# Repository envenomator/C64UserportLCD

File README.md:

# C64userport

C64 Userport LCD & LED breakout

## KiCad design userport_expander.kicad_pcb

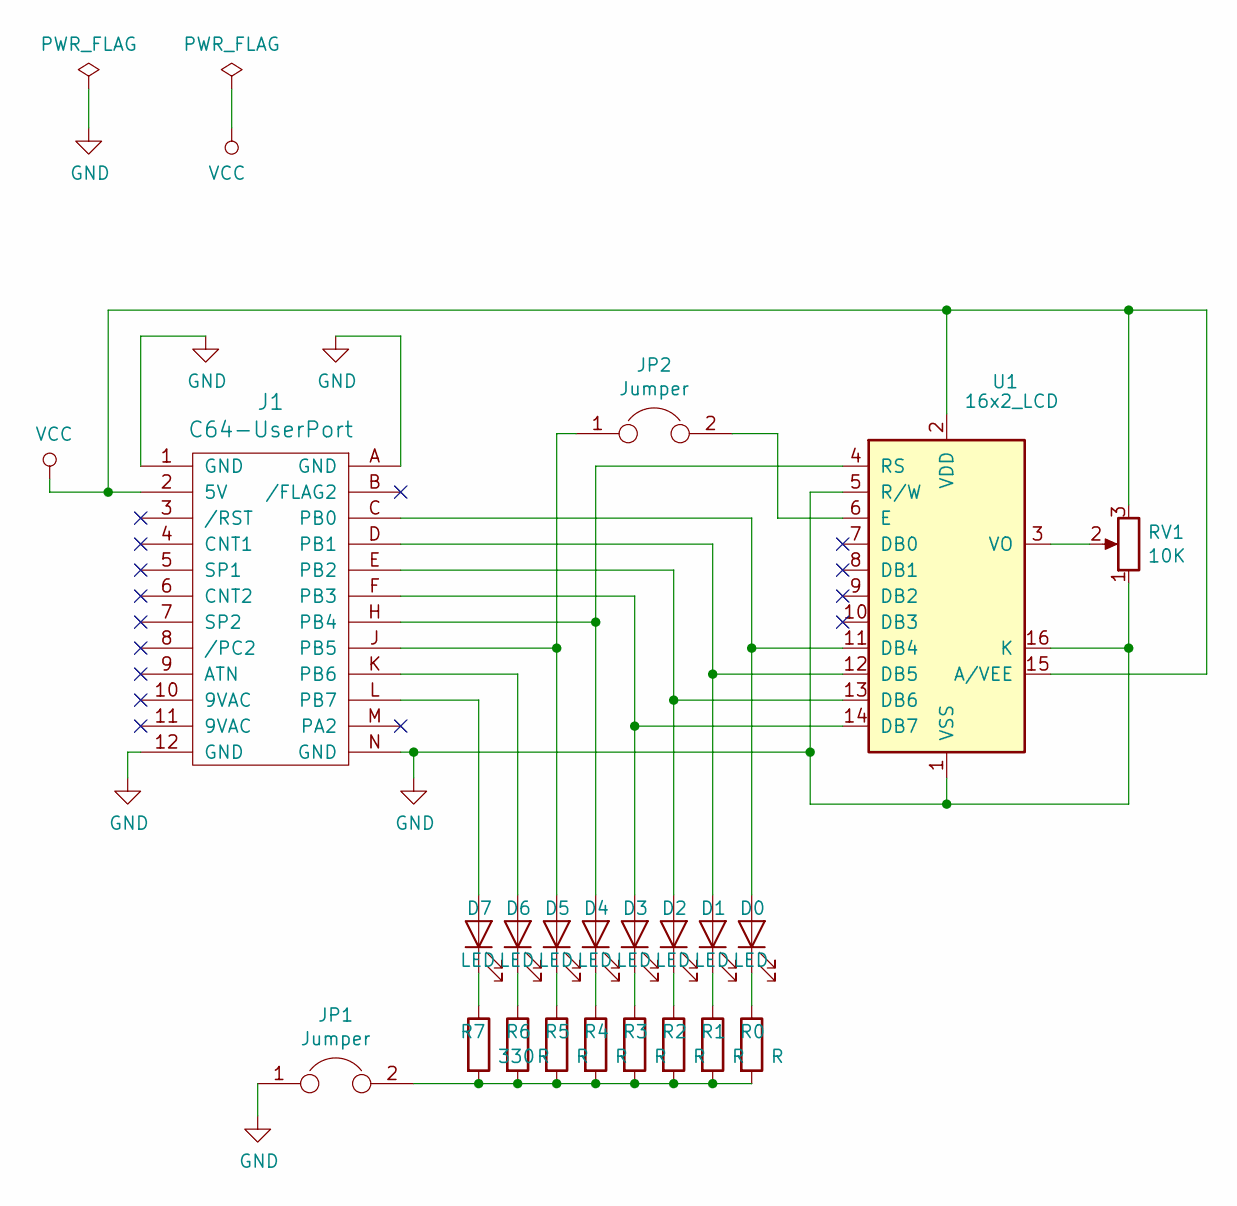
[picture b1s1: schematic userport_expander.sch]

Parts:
D0, D1, D2, D3, D4, D5, D6, D7: LED; LED_D3.0mm
J1: C64-UserPort; C64-User-Port-Female
JP1, JP2: Jumper; PinHeader_1x02_P2.54mm_Vertical
R0, R1, R2, R3, R4, R5, R6: R; R_Axial_DIN0207_L6.3mm_D2.5mm_P7.62mm_Horizontal
R7: 330; R_Axial_DIN0207_L6.3mm_D2.5mm_P7.62mm_Horizontal
RV1: 10K; Potentiometer_Bourns_3296W_Vertical
U1: 16x2_LCD; WC1602A

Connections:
GND: J1.1 (GND), J1.12 (GND), J1.A (GND), J1.N (GND), JP1.1, RV1.1, U1.1 (VSS), U1.5 (R/W), U1.16 (K)
unnamed: D0.1 (K), R0.1
unnamed: D0.2 (A), J1.C (PB0), U1.11 (DB4)
unnamed: D1.1 (K), R1.1
unnamed: D1.2 (A), J1.D (PB1), U1.12 (DB5)
unnamed: D2.1 (K), R2.1
unnamed: D2.2 (A), J1.E (PB2), U1.13 (DB6)
unnamed: D3.1 (K), R3.1
unnamed: D3.2 (A), J1.F (PB3), U1.14 (DB7)
unnamed: D4.1 (K), R4.1
unnamed: D4.2 (A), J1.H (PB4), U1.4 (RS)
unnamed: D5.1 (K), R5.1
unnamed: D5.2 (A), J1.J (PB5), JP2.1
unnamed: D6.1 (K), R6.1
unnamed: D6.2 (A), J1.K (PB6)
unnamed: D7.1 (K), R7.1
unnamed: D7.2 (A), J1.L (PB7)
unnamed: JP1.2, R0.2, R1.2, R2.2, R3.2, R4.2, R5.2, R6.2, R7.2
unnamed: JP2.2, U1.6 (E)
unnamed: RV1.2, U1.3 (VO)
VCC: J1.2 (5V), RV1.3, U1.2 (VDD), U1.15 (A/VEE)

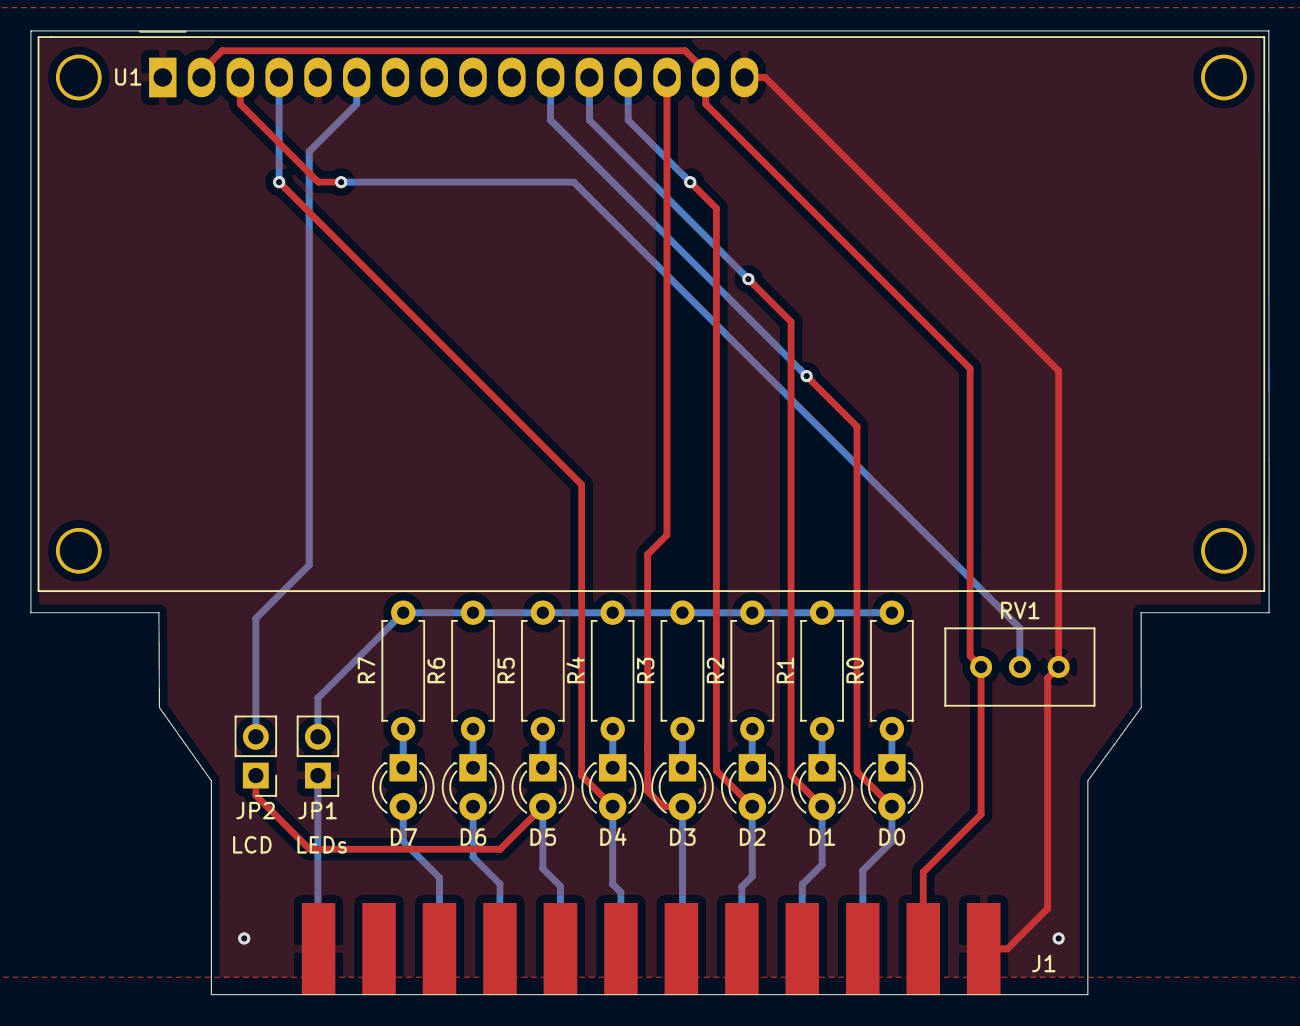
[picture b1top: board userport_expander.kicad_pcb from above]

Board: 2 copper layers, 81.1 x 63.1 mm, 21 parts (0 on the bottom side), 21 nets.

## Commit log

2020-05-12 Board v1 - as sent to PCBway
2020-05-12 Final PB <=> DB port bit mapping for 4-bit operation
2020-05-12 Fixed 4-bit PCB layout, no gerbers yet
2020-05-17 Gerbers v2 added, board sent to JCLPCB
2021-04-08 Final
2021-04-08 Photo of finished PCB
2021-04-08 Schematic to PDF export
